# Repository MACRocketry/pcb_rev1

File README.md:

# pcb_rev1
pcb for rev1, contains:  
* 10-DOF waveshare  
* SD card  
* 3v3 regulator

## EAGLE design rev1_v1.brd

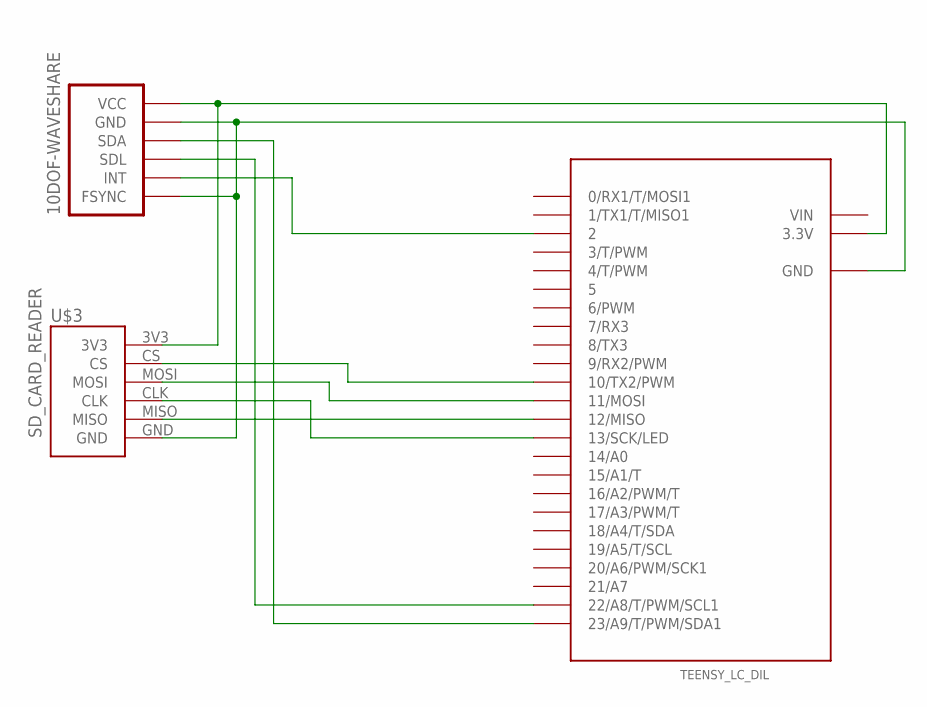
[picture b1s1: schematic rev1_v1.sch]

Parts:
U$1: TEENSY_LC_DIL; TEENSY_3.0-3.2&LC_DIL
U$2: 10DOF-WAVESHARE
U$3: SD_CARD_READER; MICRO_SD_READER_3V3

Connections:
unnamed: U$1.3.3V, U$2.VCC, U$3.3V3
unnamed: U$1.AGND (GND), U$1.GND, U$2.FSYNC, U$2.GND, U$3.GND
unnamed: U$1.23/A9 (23/A9/T/PWM/SDA1), U$2.SDA
unnamed: U$1.22/A8 (22/A8/T/PWM/SCL1), U$2.SCL (SDL)
unnamed: U$1.2, U$2.INT
unnamed: U$1.11 (11/MOSI), U$3.MOSI
unnamed: U$1.13 (13/SCK/LED), U$3.CLK
unnamed: U$1.12 (12/MISO), U$3.MISO
unnamed: U$1.10 (10/TX2/PWM), U$3.CS
VIN: U$1.VIN

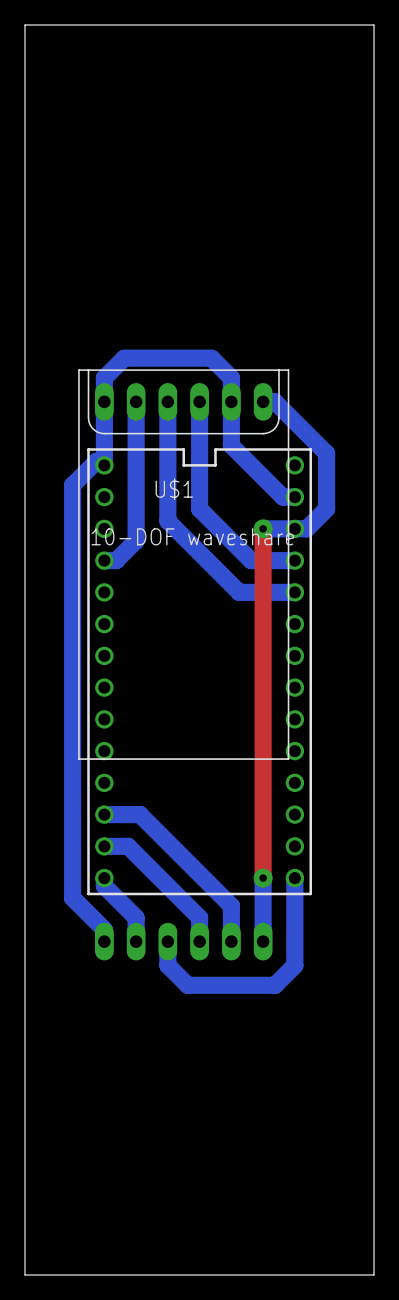
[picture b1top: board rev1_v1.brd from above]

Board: 2 copper layers, 27.9 x 100.0 mm, 3 parts (1 on the bottom side), 9 nets.

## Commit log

2019-11-03 add pcb rev1 to version control
2019-11-03 change README format
